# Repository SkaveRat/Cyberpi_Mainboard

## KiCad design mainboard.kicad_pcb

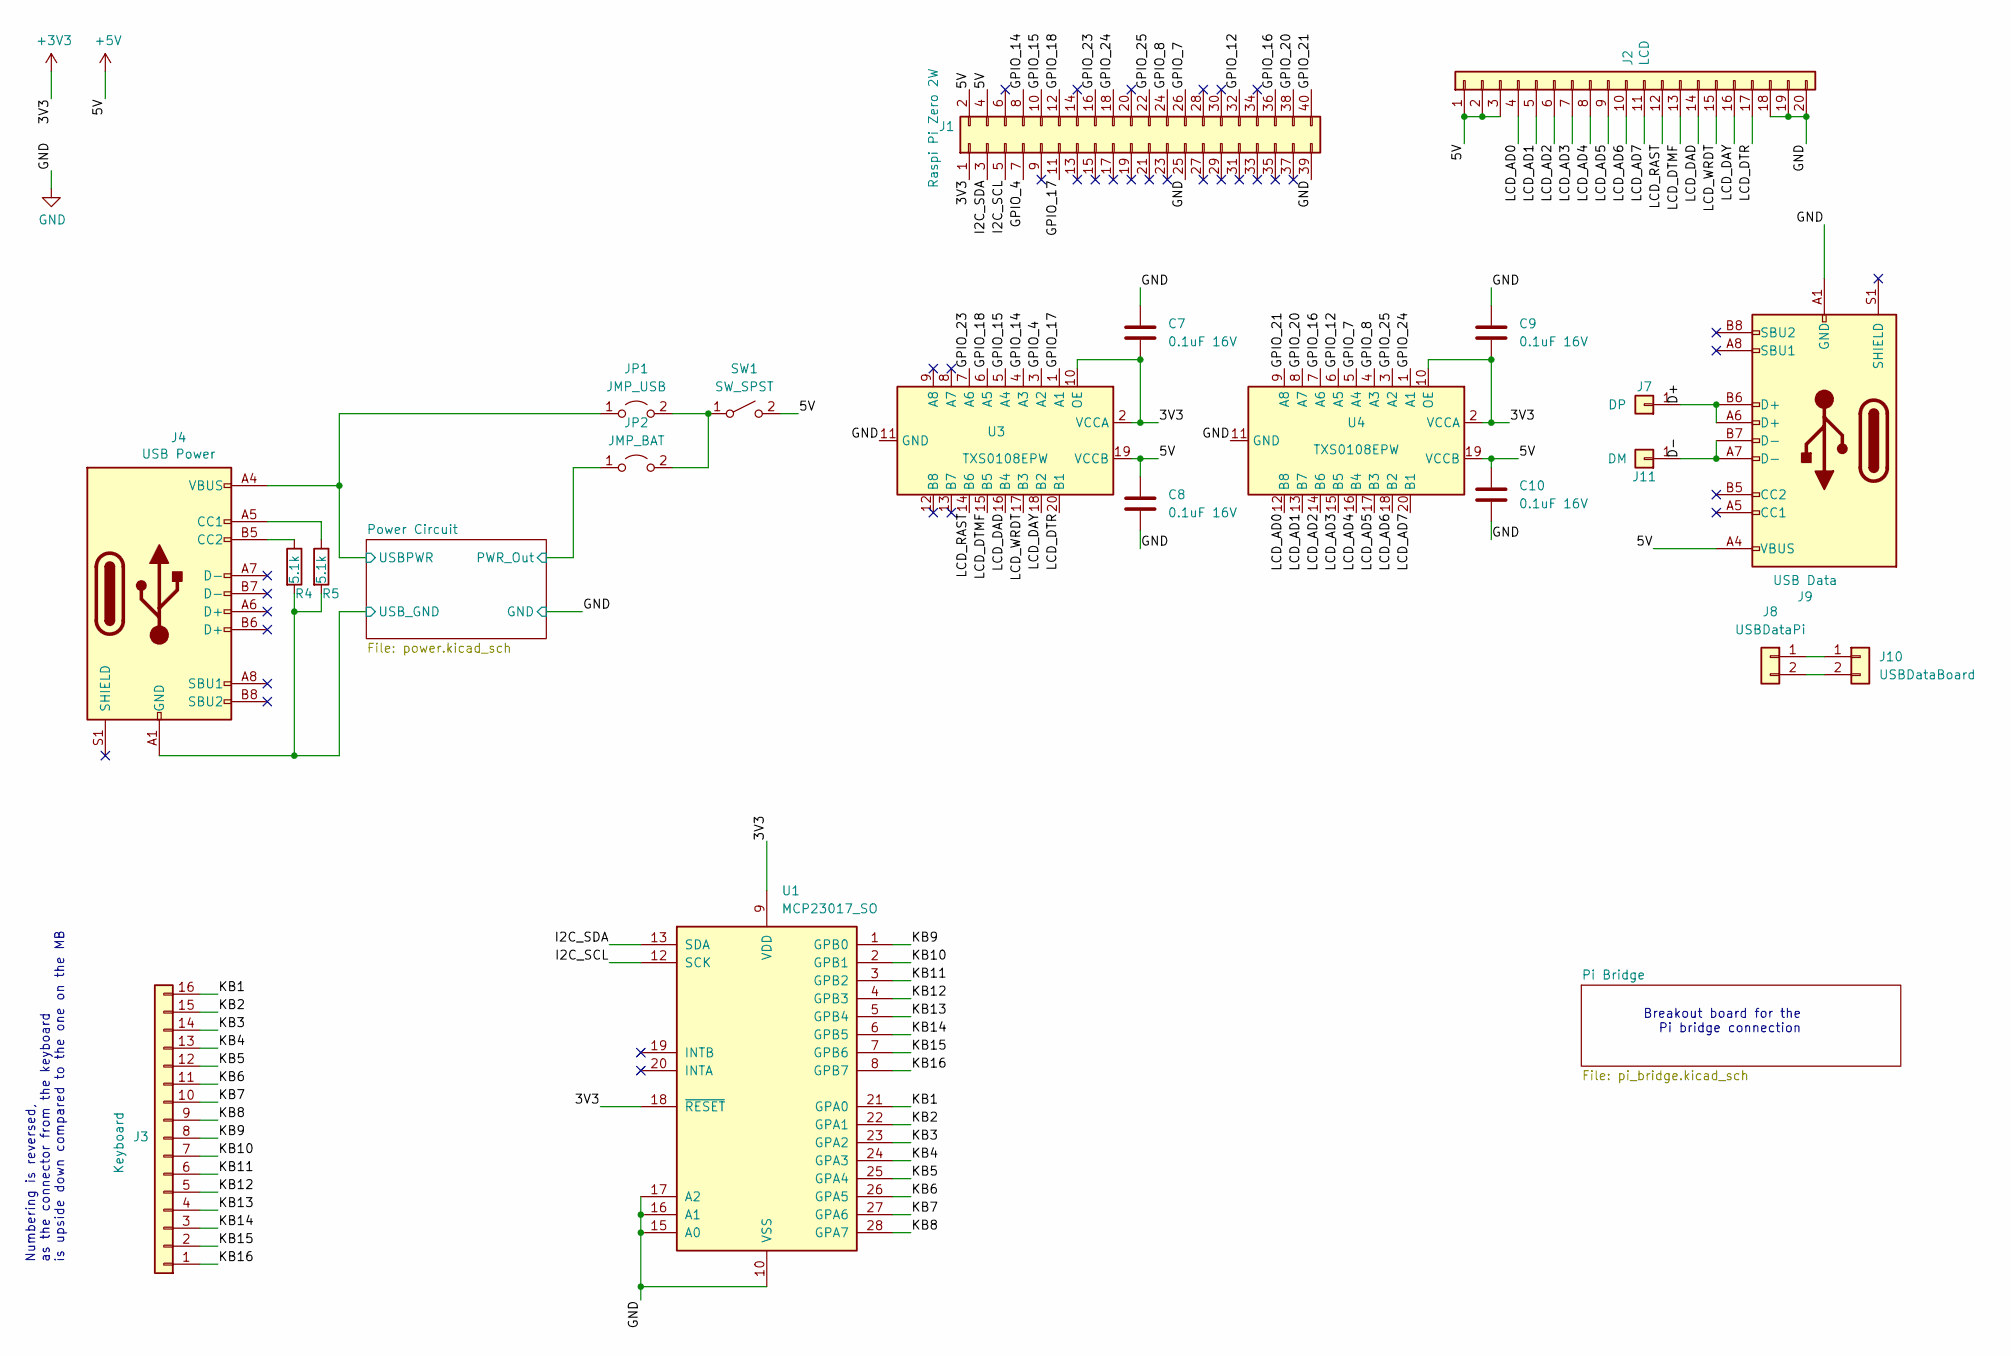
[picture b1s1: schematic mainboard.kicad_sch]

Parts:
C7, C8, C9, C10: 0.1uF 16V; C_0805_2012Metric_Pad1.18x1.45mm_HandSolder
J1: Raspi Pi Zero 2W; PinHeader_2x20_P2.54mm_Vertical
J2: LCD; TE_2-84953-0_1x20-1MP_P1.0mm_Horizontal
J3: Keyboard; TE_1-84953-6_1x16-1MP_P1.0mm_Horizontal
J4: USB Power; USB_C_Receptacle_XKB_U262-16XN-4BVC11
J7: DP; TestPoint_Pad_D1.0mm
J8: USBDataPi; PinHeader_1x02_P2.00mm_Vertical
J9: USB Data; USB_C_Receptacle_XKB_U262-16XN-4BVC11
J10: USBDataBoard; PinHeader_1x02_P2.00mm_Vertical
J11: DM; TestPoint_Pad_D1.0mm
JP1: JMP_USB; SolderJumper-2_P1.3mm_Open_RoundedPad1.0x1.5mm
JP2: JMP_BAT; SolderJumper-2_P1.3mm_Open_RoundedPad1.0x1.5mm
R4, R5: 5.1k; R_0805_2012Metric_Pad1.20x1.40mm_HandSolder
SW1: SW_SPST; SS312SAH4-R
U1: MCP23017_SO; TSSOP-28_6.1x9.7mm_P0.65mm
U3, U4: TXS0108EPW; TSSOP-20_4.4x6.5mm_P0.65mm

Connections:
+3V3: C7.2, C9.2, J1.1, U1.9 (VDD), U1.18 (~RESET), U3.2 (VCCA), U3.10 (OE), U4.2 (VCCA), U4.10 (OE)
+5V: C8.1, C10.1, J1.2, J1.4, J2.1, J2.2, J2.3, J9.A4 (VBUS), J9.A9 (VBUS), J9.B4 (VBUS), J9.B9 (VBUS), SW1.2 (B), U3.19 (VCCB), U4.19 (VCCB)
/D+: J7.1, J9.A6 (D+), J9.B6 (D+)
/D-: J9.A7 (D-), J9.B7 (D-), J11.1
/GPIO_4: J1.7, U3.3 (A2)
/GPIO_7: J1.26, U4.5 (A4)
/GPIO_8: J1.24, U4.4 (A3)
/GPIO_12: J1.32, U4.6 (A5)
/GPIO_14: J1.8, U3.4 (A3)
/GPIO_15: J1.10, U3.5 (A4)
/GPIO_16: J1.36, U4.7 (A6)
/GPIO_17: J1.11, U3.1 (A1)
/GPIO_18: J1.12, U3.6 (A5)
/GPIO_20: J1.38, U4.8 (A7)
/GPIO_21: J1.40, U4.9 (A8)
/GPIO_23: J1.16, U3.7 (A6)
/GPIO_24: J1.18, U4.1 (A1)
/GPIO_25: J1.22, U4.3 (A2)
/I2C_SCL: J1.5, U1.12 (SCK)
/I2C_SDA: J1.3, U1.13 (SDA)
/KB1: J3.16, U1.21 (GPA0)
/KB2: J3.15, U1.22 (GPA1)
/KB3: J3.14, U1.23 (GPA2)
/KB4: J3.13, U1.24 (GPA3)
/KB5: J3.12, U1.25 (GPA4)
/KB6: J3.11, U1.26 (GPA5)
/KB7: J3.10, U1.27 (GPA6)
/KB8: J3.9, U1.28 (GPA7)
/KB9: J3.8, U1.1 (GPB0)
/KB10: J3.7, U1.2 (GPB1)
/KB11: J3.6, U1.3 (GPB2)
/KB12: J3.5, U1.4 (GPB3)
/KB13: J3.4, U1.5 (GPB4)
/KB14: J3.3, U1.6 (GPB5)
/KB15: J3.2, U1.7 (GPB6)
/KB16: J3.1, U1.8 (GPB7)
/LCD_AD0: J2.4, U4.12 (B8)
/LCD_AD1: J2.5, U4.13 (B7)
/LCD_AD2: J2.6, U4.14 (B6)
/LCD_AD3: J2.7, U4.15 (B5)
/LCD_AD4: J2.8, U4.16 (B4)
/LCD_AD5: J2.9, U4.17 (B3)
/LCD_AD6: J2.10, U4.18 (B2)
/LCD_AD7: J2.11, U4.20 (B1)
/LCD_DAD: J2.14, U3.16 (B4)
/LCD_DAY: J2.16, U3.18 (B2)
/LCD_DTMF: J2.13, U3.15 (B5)
/LCD_DTR: J2.17, U3.20 (B1)
/LCD_RAST: J2.12, U3.14 (B6)
/LCD_WRDT: J2.15, U3.17 (B3)
/Power Circuit/PWR_Out: JP2.1 (A); also elsewhere on the board
/Power Circuit/USBPWR: J4.A4 (VBUS), J4.A9 (VBUS), J4.B4 (VBUS), J4.B9 (VBUS), JP1.1 (A); also elsewhere on the board
GND: C7.1, C8.2, C9.1, C10.2, J1.25, J1.39, J2.18, J2.19, J2.20, J4.A1 (GND), J4.A12 (GND), J4.B1 (GND), J4.B12 (GND), J9.A1 (GND), J9.A12 (GND), J9.B1 (GND), J9.B12 (GND), R4.2, R5.2, U1.10 (VSS), U1.15 (A0), U1.16 (A1), U1.17 (A2), U3.11 (GND), U4.11 (GND); also elsewhere on the board
unnamed: J4.A5 (CC1), R5.1
unnamed: J4.B5 (CC2), R4.1
unnamed: J8.1, J10.1
unnamed: J8.2, J10.2
unnamed: JP1.2 (B), JP2.2 (B), SW1.1 (A)

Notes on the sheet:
Breakout board for the Pi bridge connection
Numbering is reversed, as the connector from the keyboard is upside down compared to the one on the MB

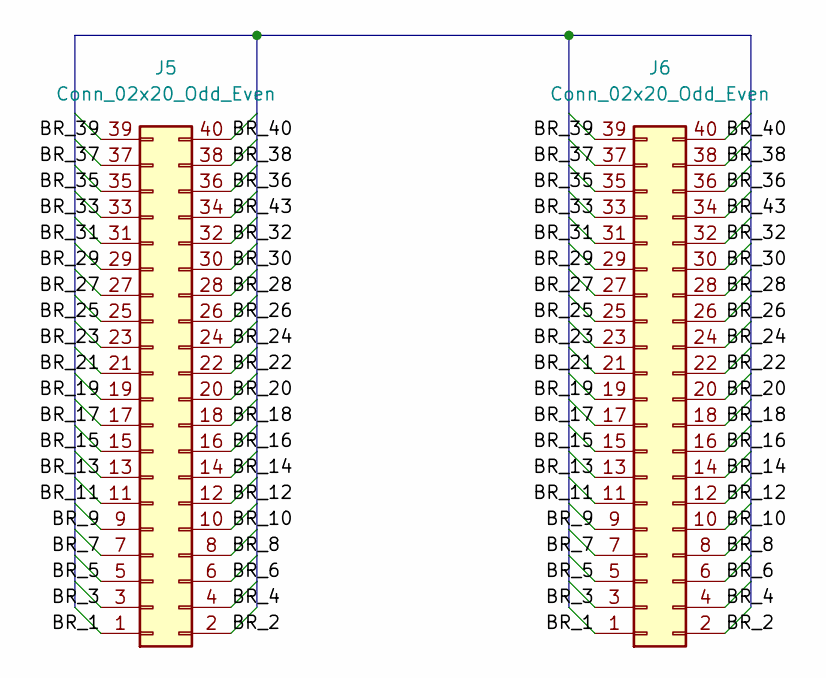
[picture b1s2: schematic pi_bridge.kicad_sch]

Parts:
J5, J6: Conn_02x20_Odd_Even; PinHeader_2x20_P2.54mm_Vertical

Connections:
/Pi Bridge/BR_1: J5.1, J6.1
/Pi Bridge/BR_2: J5.2, J6.2
/Pi Bridge/BR_3: J5.3, J6.3
/Pi Bridge/BR_4: J5.4, J6.4
/Pi Bridge/BR_5: J5.5, J6.5
/Pi Bridge/BR_6: J5.6, J6.6
/Pi Bridge/BR_7: J5.7, J6.7
/Pi Bridge/BR_8: J5.8, J6.8
/Pi Bridge/BR_9: J5.9, J6.9
/Pi Bridge/BR_10: J5.10, J6.10
/Pi Bridge/BR_11: J5.11, J6.11
/Pi Bridge/BR_12: J5.12, J6.12
/Pi Bridge/BR_13: J5.13, J6.13
/Pi Bridge/BR_14: J5.14, J6.14
/Pi Bridge/BR_15: J5.15, J6.15
/Pi Bridge/BR_16: J5.16, J6.16
/Pi Bridge/BR_17: J5.17, J6.17
/Pi Bridge/BR_18: J5.18, J6.18
/Pi Bridge/BR_19: J5.19, J6.19
/Pi Bridge/BR_20: J5.20, J6.20
/Pi Bridge/BR_21: J5.21, J6.21
/Pi Bridge/BR_22: J5.22, J6.22
/Pi Bridge/BR_23: J5.23, J6.23
/Pi Bridge/BR_24: J5.24, J6.24
/Pi Bridge/BR_25: J5.25, J6.25
/Pi Bridge/BR_26: J5.26, J6.26
/Pi Bridge/BR_27: J5.27, J6.27
/Pi Bridge/BR_28: J5.28, J6.28
/Pi Bridge/BR_29: J5.29, J6.29
/Pi Bridge/BR_30: J5.30, J6.30
/Pi Bridge/BR_31: J5.31, J6.31
/Pi Bridge/BR_32: J5.32, J6.32
/Pi Bridge/BR_33: J5.33, J6.33
/Pi Bridge/BR_35: J5.35, J6.35
/Pi Bridge/BR_36: J5.36, J6.36
/Pi Bridge/BR_37: J5.37, J6.37
/Pi Bridge/BR_38: J5.38, J6.38
/Pi Bridge/BR_39: J5.39, J6.39
/Pi Bridge/BR_40: J5.40, J6.40
/Pi Bridge/BR_43: J5.34, J6.34

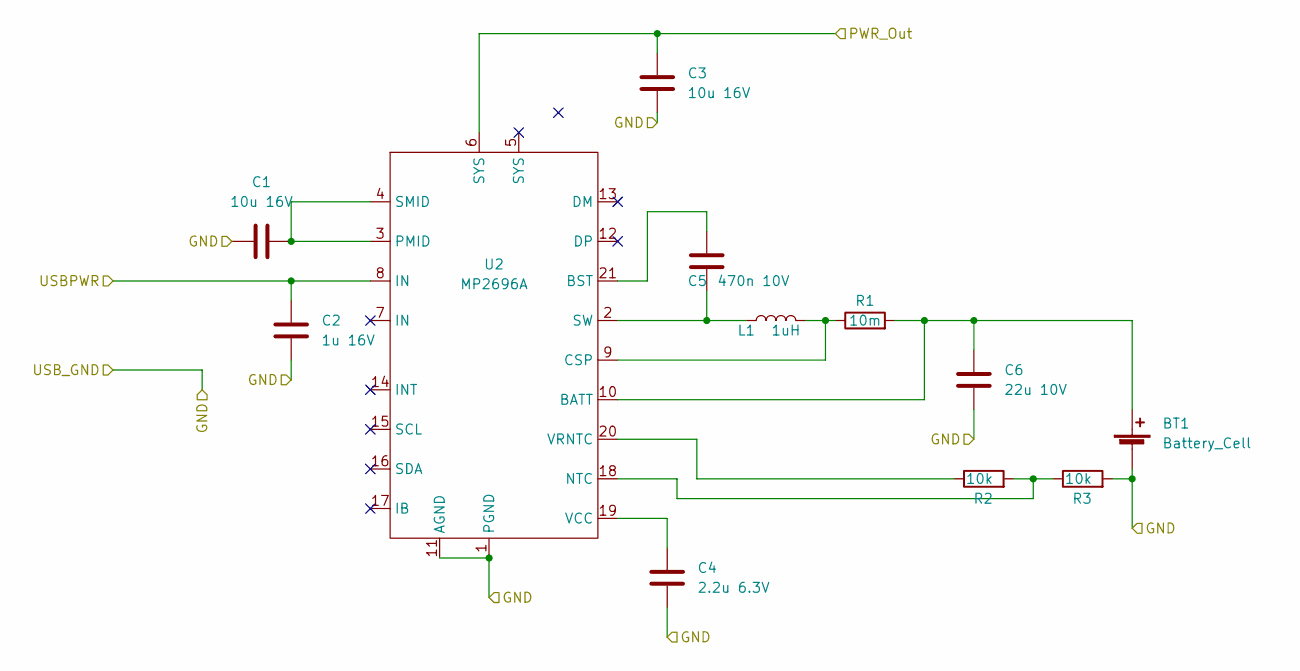
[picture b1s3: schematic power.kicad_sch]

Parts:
BT1: Battery_Cell; Molex_MicroClasp_55932-0230_1x02_P2.00mm_Vertical
C1, C3: 10u 16V; C_0805_2012Metric_Pad1.18x1.45mm_HandSolder
C2: 1u 16V; C_0805_2012Metric_Pad1.18x1.45mm_HandSolder
C4: 2.2u 6.3V; C_0805_2012Metric_Pad1.18x1.45mm_HandSolder
C5: 470n 10V; C_0805_2012Metric_Pad1.18x1.45mm_HandSolder
C6: 22u 10V; C_0805_2012Metric_Pad1.18x1.45mm_HandSolder
L1: 1uH; L_12x12mm_H4.5mm
R1: 10m; R_0805_2012Metric_Pad1.20x1.40mm_HandSolder
R2, R3: 10k; R_0805_2012Metric_Pad1.20x1.40mm_HandSolder
U2: MP2696A; QFN-21

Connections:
/Power Circuit/PWR_Out: C3.1, U2.6 (SYS); also elsewhere on the board
/Power Circuit/USBPWR: C2.1, U2.8 (IN); also elsewhere on the board
GND: BT1.1 (-), C1.1, C2.2, C3.2, C4.2, C6.2, R3.2, U2.1 (PGND), U2.11 (AGND); also elsewhere on the board
unnamed: BT1.2 (+), C6.1, R1.2, U2.10 (BATT)
unnamed: C1.2, U2.3 (PMID), U2.4 (SMID)
unnamed: C4.1, U2.19 (VCC)
unnamed: C5.1, U2.21 (BST)
unnamed: C5.2, L1.1, U2.2 (SW)
unnamed: L1.2, R1.1, U2.9 (CSP)
unnamed: R2.1, U2.20 (VRNTC)
unnamed: R2.2, R3.1, U2.18 (NTC)

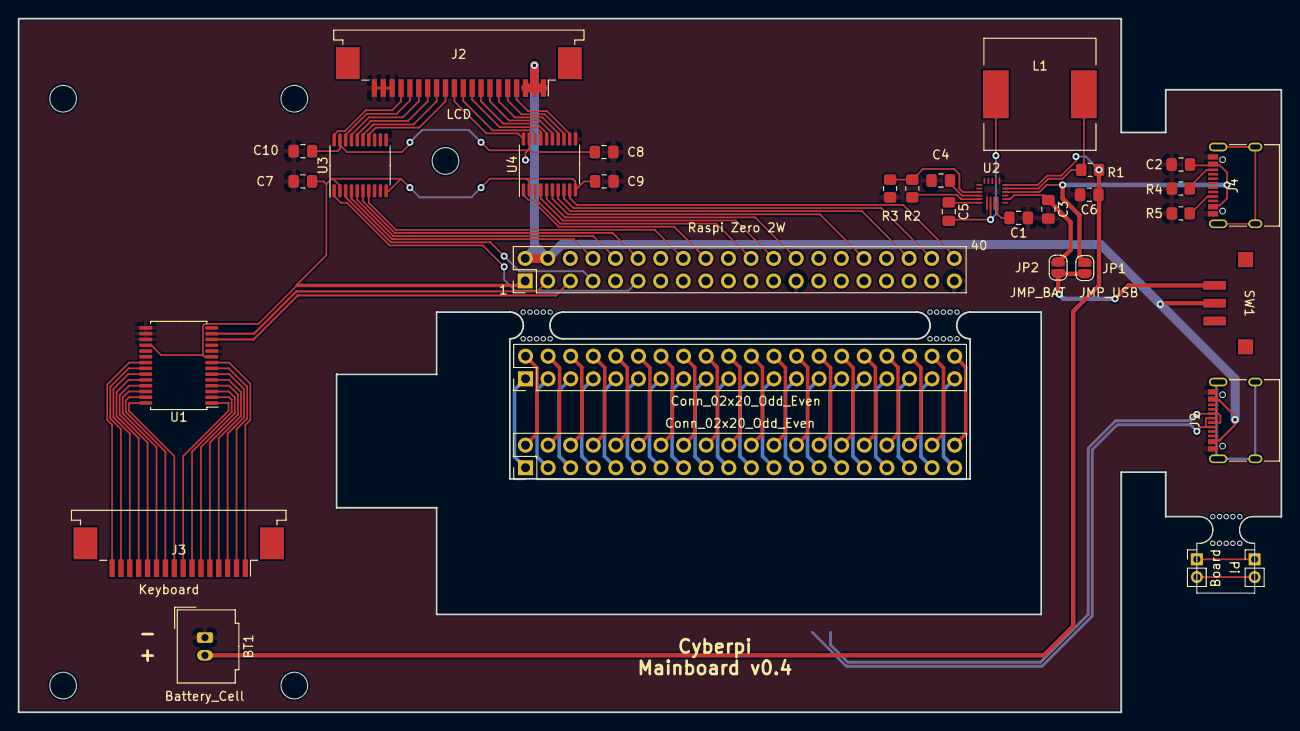
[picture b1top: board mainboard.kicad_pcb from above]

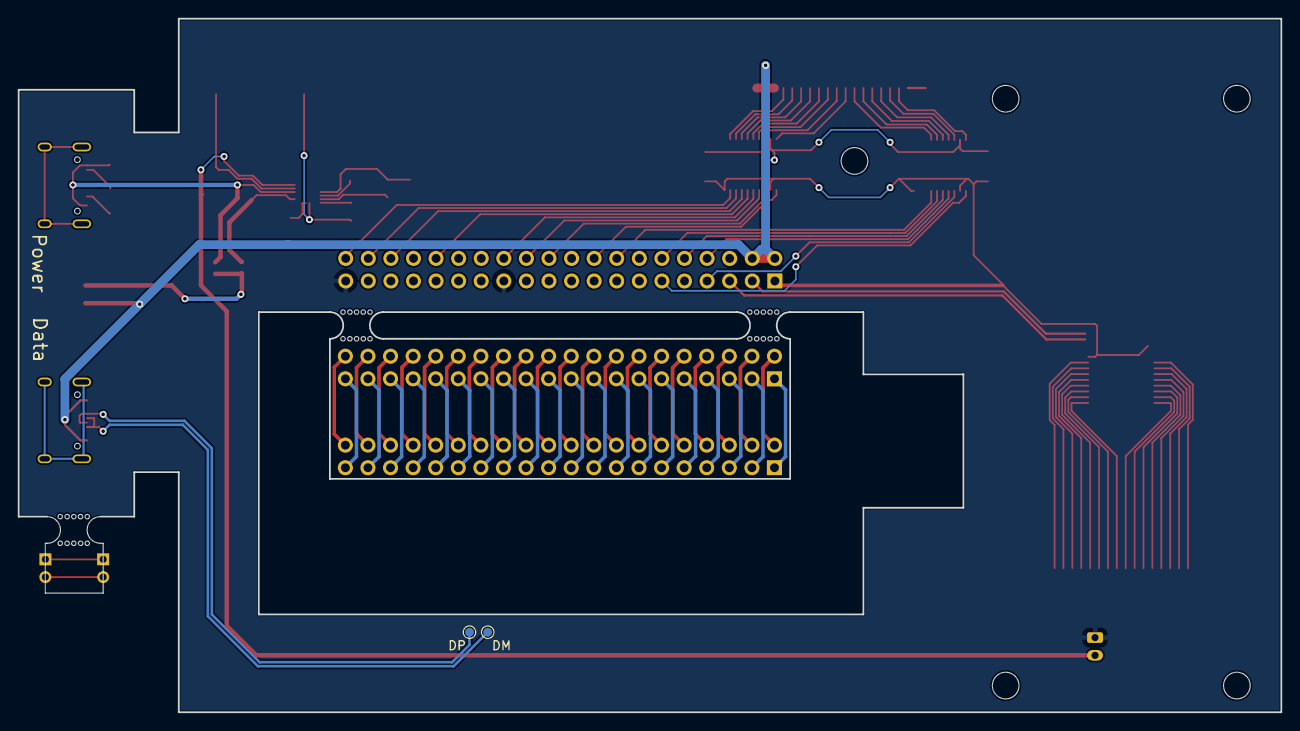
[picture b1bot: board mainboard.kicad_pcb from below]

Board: 2 copper layers, 142.0 x 78.0 mm, 38 parts (2 on the bottom side), 106 nets.

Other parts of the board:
mouse-bite-3mm-slot, mouse-bite-3mm-slot#2, mouse-bite-3mm-slot#3: VAL**; mouse-bite-3mm-slot

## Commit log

2022-04-27 init
2022-04-27 Initial version
2022-04-30 adding logic converter and power supply
2022-05-02 Adding switch to power
2022-05-16 v0.2
2022-05-27 updating footprint
2022-06-24 adding bypass caps to level shifter
